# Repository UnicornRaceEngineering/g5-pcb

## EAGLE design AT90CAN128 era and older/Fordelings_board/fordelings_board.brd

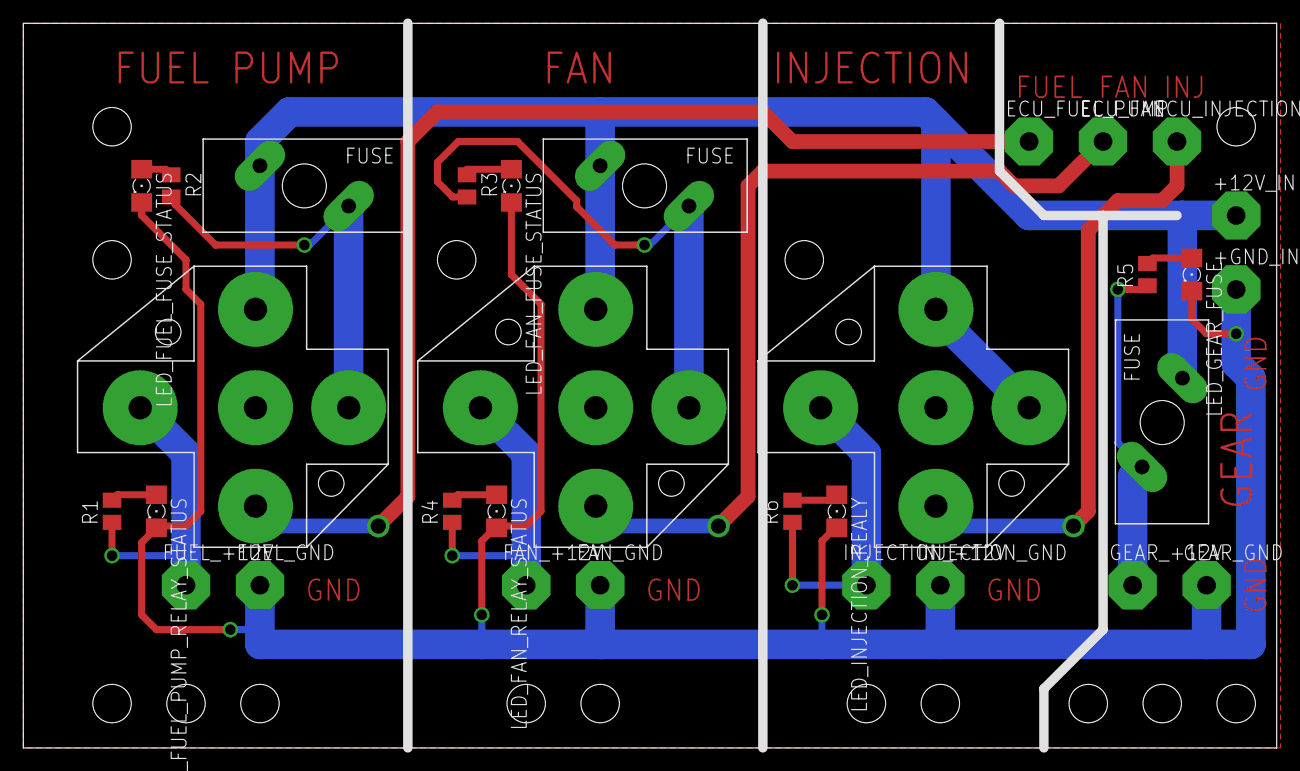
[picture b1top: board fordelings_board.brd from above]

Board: 2 copper layers, 107.6 x 62.2 mm, 46 parts (0 on the bottom side), 17 nets.

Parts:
+12V_IN: WIREPAD4,16O1,6; 4,16O1,6
+GND_IN: WIREPAD4,16O1,6; 4,16O1,6
ECU_FAN: WIREPAD4,16O1,6; 4,16O1,6
ECU_FUEL_PUMP: WIREPAD4,16O1,6; 4,16O1,6
ECU_INJECTION: WIREPAD4,16O1,6; 4,16O1,6
FAN_+12V: WIREPAD4,16O1,6; 4,16O1,6
FAN_GND: WIREPAD4,16O1,6; 4,16O1,6
FUEL_+12V: WIREPAD4,16O1,6; 4,16O1,6
FUEL_GND: WIREPAD4,16O1,6; 4,16O1,6
FUEL_PUMP_RELAY: FUSE_SOCKET; FUSE_SOCKET_12V_30A
GEAR_+12V: WIREPAD4,16O1,6; 4,16O1,6
GEAR_GND: WIREPAD4,16O1,6; 4,16O1,6
INJECTION_+12V: WIREPAD4,16O1,6; 4,16O1,6
INJECTION_GND: WIREPAD4,16O1,6; 4,16O1,6
JP1, JP2, JP3, JP4, JP5, JP6, JP7, JP8, JP9, JP10, JP11, JP12, JP13, JP14, JP15: STAND-OFF
LED_FAN_FUSE_STATUS: 1206
LED_FAN_RELAY_STATUS: 1206
LED_FUEL_FUSE_STATUS: 1206
LED_FUEL_PUMP_RELAY_STATUS: 1206
LED_GEAR_FUSE: 1206
LED_INJECTION_REALY: 1206
R1, R2, R3, R4, R5, R6: M0805
U$1, U$2: FUSE_SOCKET; FUSE_SOCKET_12V_30A
U$3, U$4, U$5: LITTE_FUSE; LITTE_FUSE_PAC

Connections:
+12V: +12V_IN.1, FUEL_PUMP_RELAY.P$4, U$1.P$1, U$1.P$4, U$2.P$4, U$3.P$1, U$4.P$2, U$5.P$2
ECU_FAN: ECU_FAN.1, U$2.P$2
ECU_FUEL_PUMP: ECU_FUEL_PUMP.1, FUEL_PUMP_RELAY.P$2
ECU_INJECTION: ECU_INJECTION.1, U$1.P$2
unnamed: FUEL_PUMP_RELAY.P$1, R2.2, U$4.P$1
unnamed: LED_FUEL_FUSE_STATUS.A, R2.1
unnamed: LED_FAN_RELAY_STATUS.A, R4.2
unnamed: R3.2, U$2.P$1, U$5.P$1
unnamed: INJECTION_+12V.1, R6.1, U$1.P$5
unnamed: GEAR_+12V.1, R5.1, U$3.P$2
unnamed: LED_GEAR_FUSE.A, R5.2
unnamed: LED_INJECTION_REALY.A, R6.2
unnamed: FAN_+12V.1, R4.1, U$2.P$5
unnamed: LED_FUEL_PUMP_RELAY_STATUS.A, R1.2
unnamed: FUEL_+12V.1, FUEL_PUMP_RELAY.P$5, R1.1
unnamed: LED_FAN_FUSE_STATUS.A, R3.1
PE: +GND_IN.1, FAN_GND.1, FUEL_GND.1, GEAR_GND.1, INJECTION_GND.1, LED_FAN_FUSE_STATUS.C, LED_FAN_RELAY_STATUS.C, LED_FUEL_FUSE_STATUS.C, LED_FUEL_PUMP_RELAY_STATUS.C, LED_GEAR_FUSE.C, LED_INJECTION_REALY.C

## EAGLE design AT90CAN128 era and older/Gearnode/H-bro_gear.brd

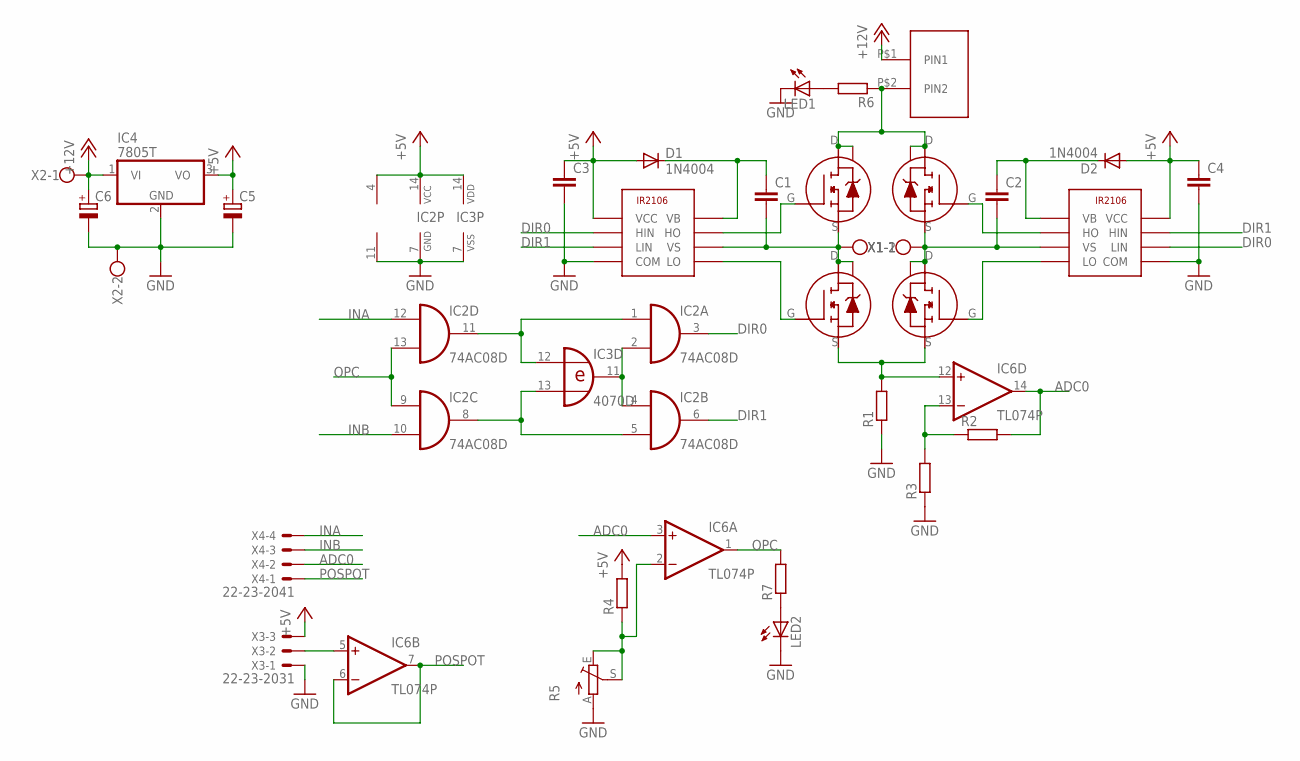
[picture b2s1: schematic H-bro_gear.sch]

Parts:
C1, C2, C3, C4: C-EU050-025X075; C050-025X075
C5, C6: CPOL-EUE15-5AXIAL; E15-5
D1, D2: 1N4004; DO41-10
IC2: 74AC08D; SO14
IC3: 4070D; SO14
IC4: 7805T; TO220H
IC6: TL074P; DIL14
LED1, LED2: LED5MM
R1: R-EU_0309/12; 0309/12
R2, R3, R4, R6, R7: R-EU_0204/7; 0204/7
R5: TRIM_EU-RJ9W; RJ9W
U$1, U$2: IR2106
U$3, U$4, U$5, U$6: STU95N5
U$7: LITTE_FUSE; LITTE_FUSE_PAC
X1, X2: W237-102
X3: 22-23-2031
X4: 22-23-2041

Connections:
+5V: C3.1, C4.1, C5.+, D1.A, D2.A, IC2.14 (VCC), IC3.14 (VDD), IC4.3 (VO), IC6.4 (V+), R4.2, U$1.VCC, U$2.VCC, X3.3
+12V: C6.+, IC4.1 (VI), U$7.P$1 (PIN1), X2.1
ADC0: IC6.3 (+IN), IC6.14 (OUT), R2.2, X4.2
DIR0: IC2.3 (O), U$1.HIN, U$2.LIN
DIR1: IC2.6 (O), U$1.LIN, U$2.HIN
GND: C3.2, C4.2, C5.-, C6.-, IC2.7 (GND), IC3.7 (VSS), IC4.2 (GND), IC6.11 (V-), LED1.K (C), LED2.K (C), R1.1, R3.1, R5.A, U$1.COM, U$2.COM, X2.2, X3.1
INA: IC2.12 (I0), X4.4
INB: IC2.10 (I1), X4.3
unnamed: U$1.HO, U$3.G
unnamed: U$1.LO, U$4.G
unnamed: U$2.HO, U$6.G
unnamed: U$2.LO, U$5.G
unnamed: C1.2, U$1.VS, U$3.S, U$4.D, U$4.TAB, X1.2
unnamed: C2.2, U$2.VS, U$5.D, U$5.TAB, U$6.S, X1.1
unnamed: R6.1, U$3.D, U$3.TAB, U$6.D, U$6.TAB, U$7.P$2 (PIN2)
unnamed: C1.1, D1.C, U$1.VB
unnamed: IC6.12 (+IN), R1.2, U$4.S, U$5.S
unnamed: C2.1, D2.C, U$2.VB
unnamed: IC2.2 (I1), IC2.4 (I0), IC3.11 (O)
unnamed: IC2.1 (I0), IC2.11 (O), IC3.12 (I0)
unnamed: IC2.5 (I1), IC2.8 (O), IC3.13 (I1)
unnamed: IC6.2 (-IN), R4.1, R5.E, R5.S
unnamed: LED1.A, R6.2
unnamed: IC6.5 (+IN), X3.2
unnamed: IC6.13 (-IN), R2.1, R3.2
unnamed: LED2.A, R7.1
OPC: IC2.9 (I0), IC2.13 (I1), IC6.1 (OUT), R7.2
POSPOT: IC6.6 (-IN), IC6.7 (OUT), X4.1

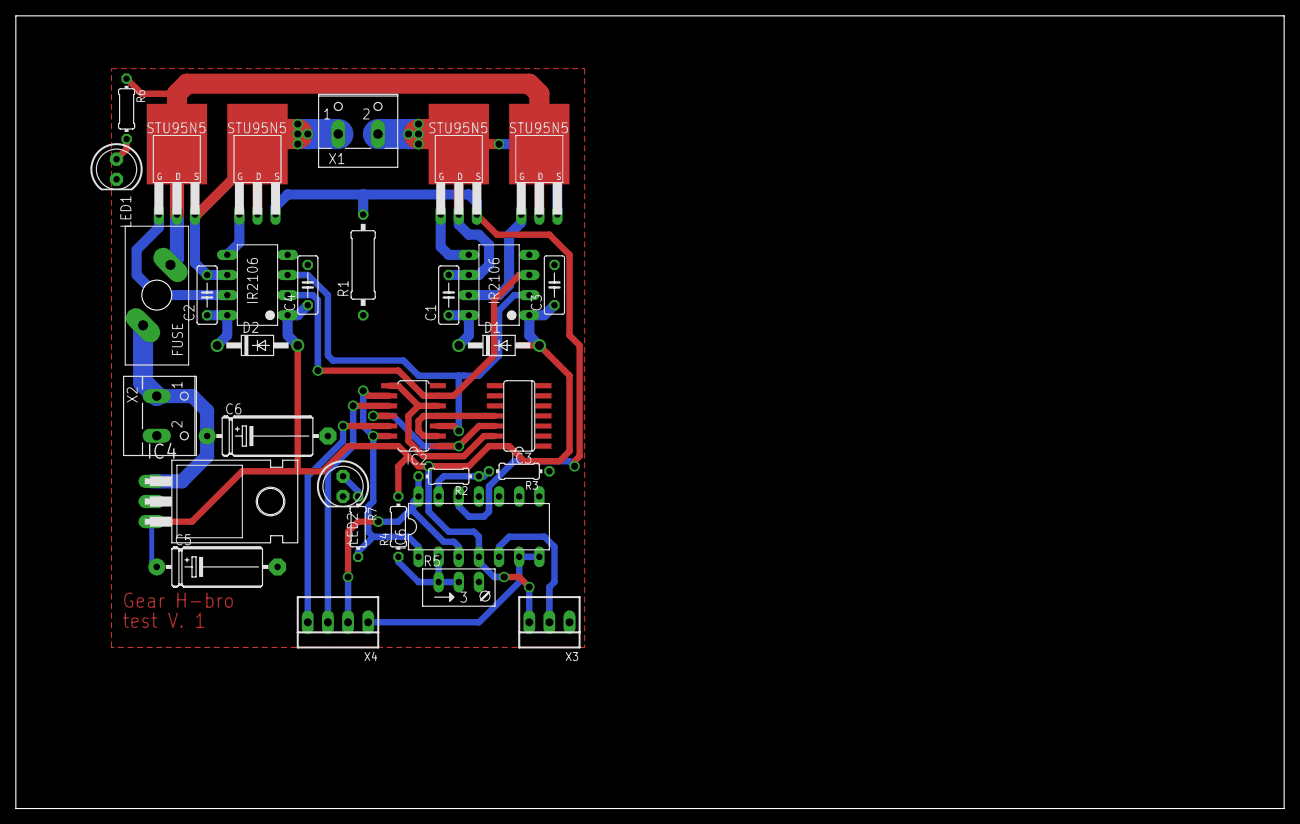
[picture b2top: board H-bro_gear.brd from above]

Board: 2 copper layers, 160.0 x 100.0 mm, 32 parts (0 on the bottom side), 28 nets.

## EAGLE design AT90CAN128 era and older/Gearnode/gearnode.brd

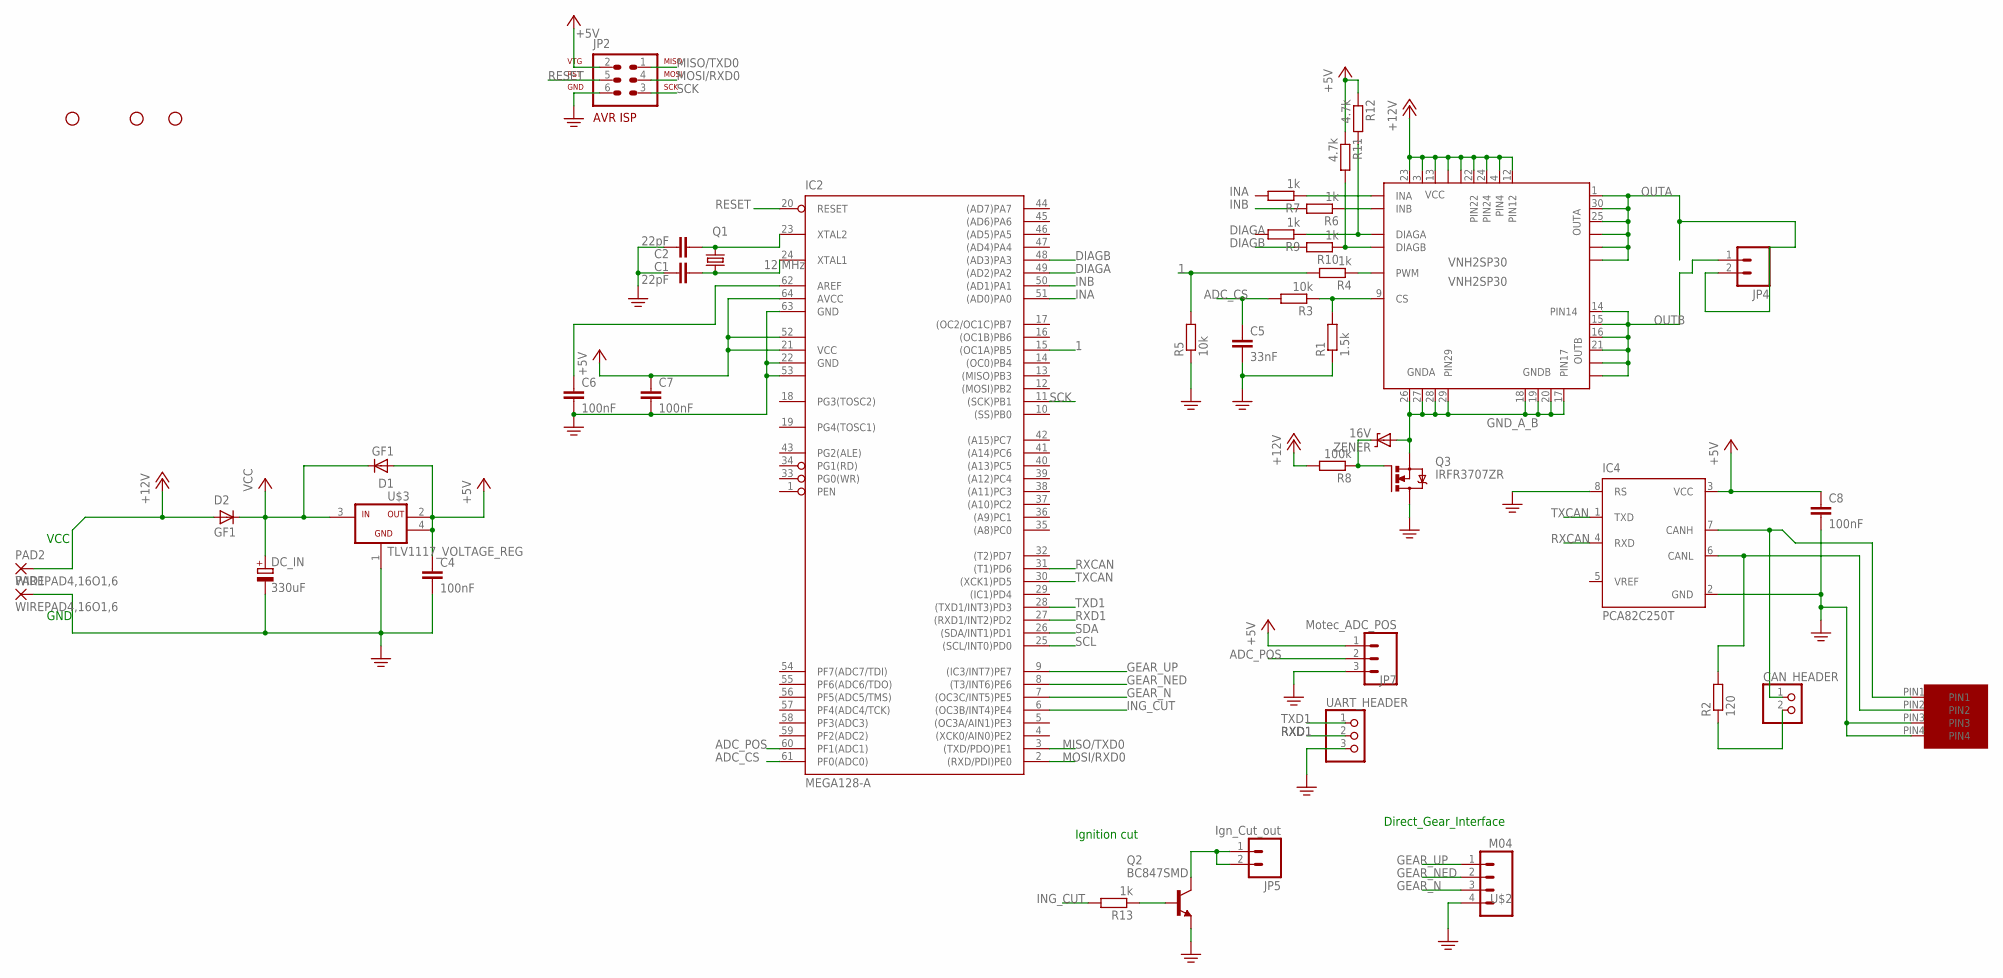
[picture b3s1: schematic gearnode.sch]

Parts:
C1, C2: 22pF; C5B2.5
C4, C6, C7, C8: 100nF; C0603K
C5: 33nF; C0603K
CAN_HEADER: PINHD-1X2; 1X02
D1, D2: GF1; SMA-DO214AC
DC_IN: 330uF; E15-5
IC2: MEGA128-A; TQFP64
IC4: PCA82C250T; SO8
JP1, JP3, JP6: STAND-OFF
JP2: AVR-ISP-6
JP4: M025MM; SCREWTERMINAL-5MM-2
JP5: Ign_Cut_out; S2B-PH
JP7: Motec_ADC_POS; S3B-PH
PAD1, PAD2: WIREPAD4,16O1,6; 4,16O1,6
Q1: 12 MHz; HC49U70
Q2: BC847SMD; SOT23
Q3: IRFR3707ZR; D-PAK_TO252AA
R1: 1.5k; R0603
R2: 120; R0603
R3, R5: 10k; R0603
R4, R6, R7, R9, R10, R13: 1k; R0603
R8: 100k; R0603
R11, R12: 4.7k; R0603
U$1: MICROFIT4; MICROFIT4SOCK
U$2: M04; S4B-PH
U$3: TLV1117_VOLTAGE_REG; SOT-232
UART_HEADER: PINHD-1X3; 1X03
VNH2SP30: VNH2SP30; MULTIPOWERSO-30
ZENER: 16V; SOD-323

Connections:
1: IC2.15 ((OC1A)PB5), R4.2, R5.2
+5V: C4.1, C7.1, C8.1, D1.A, IC2.21 (VCC), IC2.52 (VCC1), IC2.64 (AVCC), IC4.3 (VCC), JP2.2, JP7.1, R11.1, R12.1, U$3.2 (VOUT), U$3.4 (OUT2)
+12V: D2.A, PAD2.1, R8.2, VNH2SP30.3 (VCC), VNH2SP30.4 (PIN4), VNH2SP30.12 (PIN12), VNH2SP30.13 (VCC), VNH2SP30.22 (PIN22), VNH2SP30.23 (VCC), VNH2SP30.24 (PIN24), VNH2SP30.VCC, VNH2SP30.VCC@1 (VCC)
ADC_CS: C5.1, IC2.61 (PF0(ADC0)), R3.2
ADC_POS: IC2.60 (PF1(ADC1)), JP7.2
CANJUMP1: CAN_HEADER.1, IC4.7 (CANH), U$1.PIN1
CANJUMP2: CAN_HEADER.2, R2.1
DIAGA: IC2.49 ((AD2)PA2), R9.2
DIAGB: IC2.48 ((AD3)PA3), R10.2
GEAR_N: IC2.7 ((OC3C/INT5)PE5), U$2.3
GEAR_NED: IC2.8 ((T3/INT6)PE6), U$2.2
GEAR_UP: IC2.9 ((IC3/INT7)PE7), U$2.1
GND_A_B: Q3.3 (S), VNH2SP30.17 (PIN17), VNH2SP30.18 (GNDB), VNH2SP30.19 (GNDB), VNH2SP30.20 (GNDB), VNH2SP30.26 (GNDA), VNH2SP30.27 (GNDA), VNH2SP30.28 (GNDA), VNH2SP30.29 (PIN29), ZENER.2 (A)
INA: IC2.51 ((AD0)PA0), R7.2
INB: IC2.50 ((AD1)PA1), R6.2
ING_CUT: IC2.6 ((OC3B/INT4)PE4), R13.2
MISO/TXD0: IC2.3 ((TXD/PDO)PE1), JP2.1
MOSI/RXD0: IC2.2 ((RXD/PDI)PE0), JP2.4
unnamed: C1.2, IC2.24 (XTAL1), Q1.1
unnamed: C2.2, IC2.23 (XTAL2), Q1.2
unnamed: R4.1, VNH2SP30.8 (PWM)
unnamed: R1.2, R3.1, VNH2SP30.9 (CS)
unnamed: Q3.1 (G), R8.1, ZENER.1 (C)
unnamed: Q2.1 (B), R13.1
unnamed: C6.1, IC2.62 (AREF)
unnamed: JP5.1, JP5.2, Q2.3 (C)
unnamed: R9.1, R12.2, VNH2SP30.6 (DIAGA)
unnamed: R10.1, R11.2, VNH2SP30.10 (DIAGB)
unnamed: R7.1, VNH2SP30.5 (INA)
unnamed: R6.1, VNH2SP30.11 (INB)
unnamed: IC4.6 (CANL), R2.2, U$1.PIN2
OUTA: JP4.2, VNH2SP30.1 (OUTA), VNH2SP30.2 (PIN2), VNH2SP30.25 (OUTA), VNH2SP30.30 (OUTA), VNH2SP30.OUTA, VNH2SP30.OUTA@1 (OUTA)
OUTB: JP4.1, VNH2SP30.14 (PIN14), VNH2SP30.15 (OUTB), VNH2SP30.16 (OUTB), VNH2SP30.21 (OUTB), VNH2SP30.OUTB, VNH2SP30.OUTB@1 (OUTB)
PE: C1.1, C2.1, C4.2, C5.2, C6.2, C7.2, C8.2, DC_IN.-, IC2.22 (GND), IC2.53 (GND1), IC2.63 (GND), IC4.2 (GND), IC4.8 (RS), JP2.6, JP7.3, PAD1.1, Q2.2 (E), Q3.4 (D), R1.1, R5.1, U$1.PIN3, U$1.PIN4, U$2.4, U$3.1 (GND), UART_HEADER.3
RESET: IC2.20 (RESET), JP2.5
RXCAN: IC2.31 ((T1)PD6), IC4.4 (RXD)
RXD1: IC2.27 ((RXD1/INT2)PD2), UART_HEADER.2
SCK: IC2.11 ((SCK)PB1), JP2.3
SCL: IC2.25 ((SCL/INT0)PD0)
SDA: IC2.26 ((SDA/INT1)PD1)
TXCAN: IC2.30 ((XCK1)PD5), IC4.1 (TXD)
TXD1: IC2.28 ((TXD1/INT3)PD3), UART_HEADER.1
VCC: D1.K (C), D2.K (C), DC_IN.+, U$3.3 (VIN)

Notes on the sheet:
VCC
GND
Ignition cut
Direct_Gear_Interface

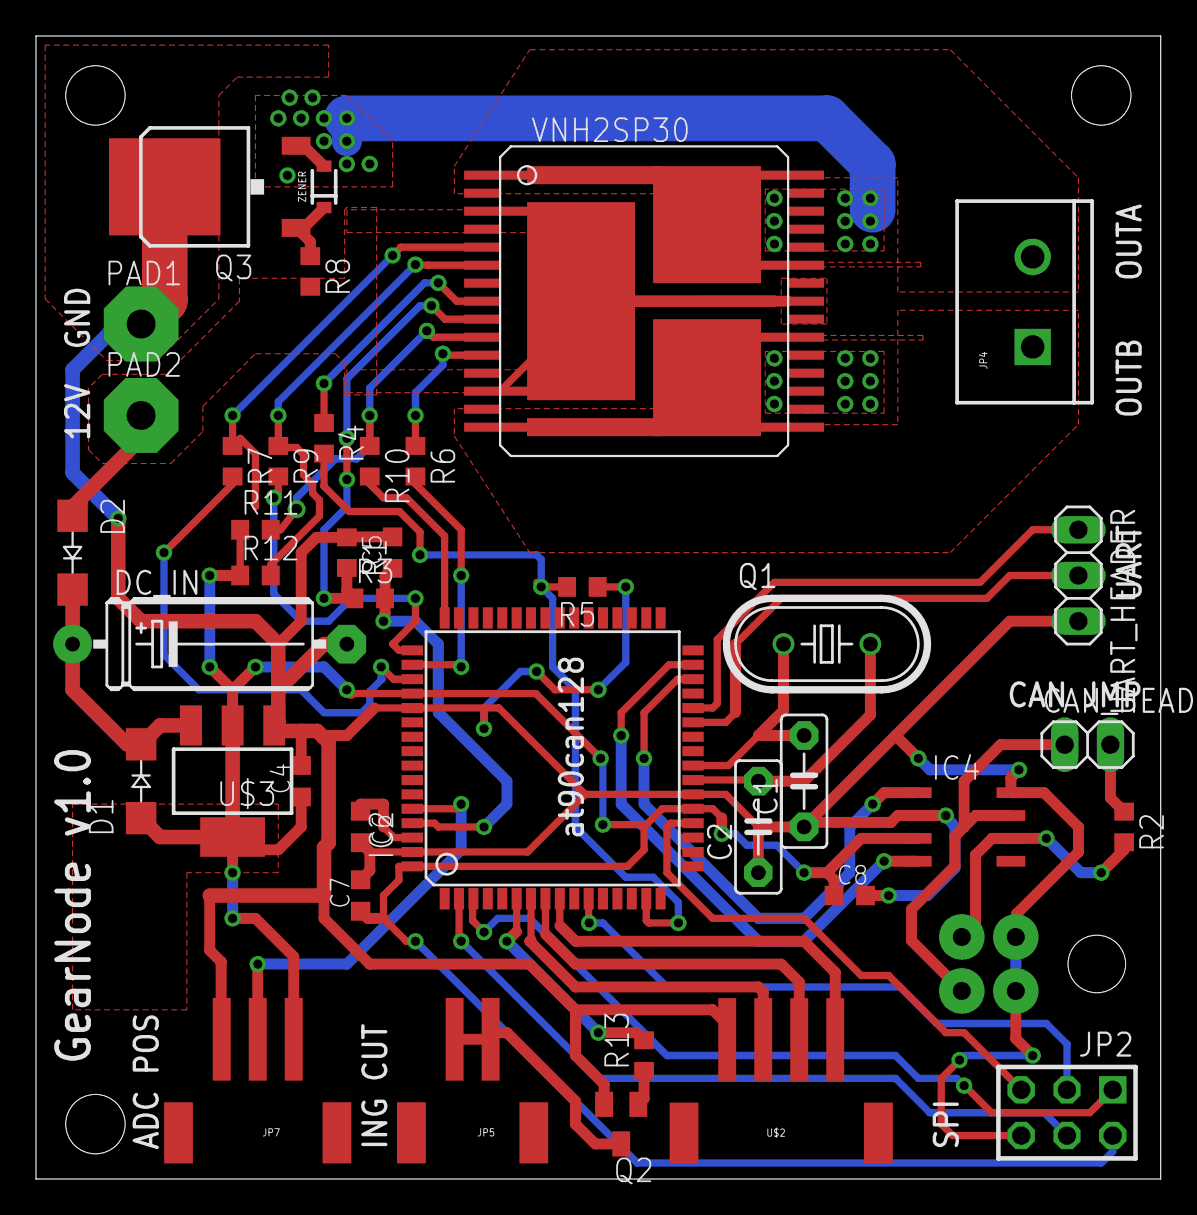
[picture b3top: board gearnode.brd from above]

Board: 2 copper layers, 62.5 x 63.5 mm, 44 parts (0 on the bottom side), 41 nets.

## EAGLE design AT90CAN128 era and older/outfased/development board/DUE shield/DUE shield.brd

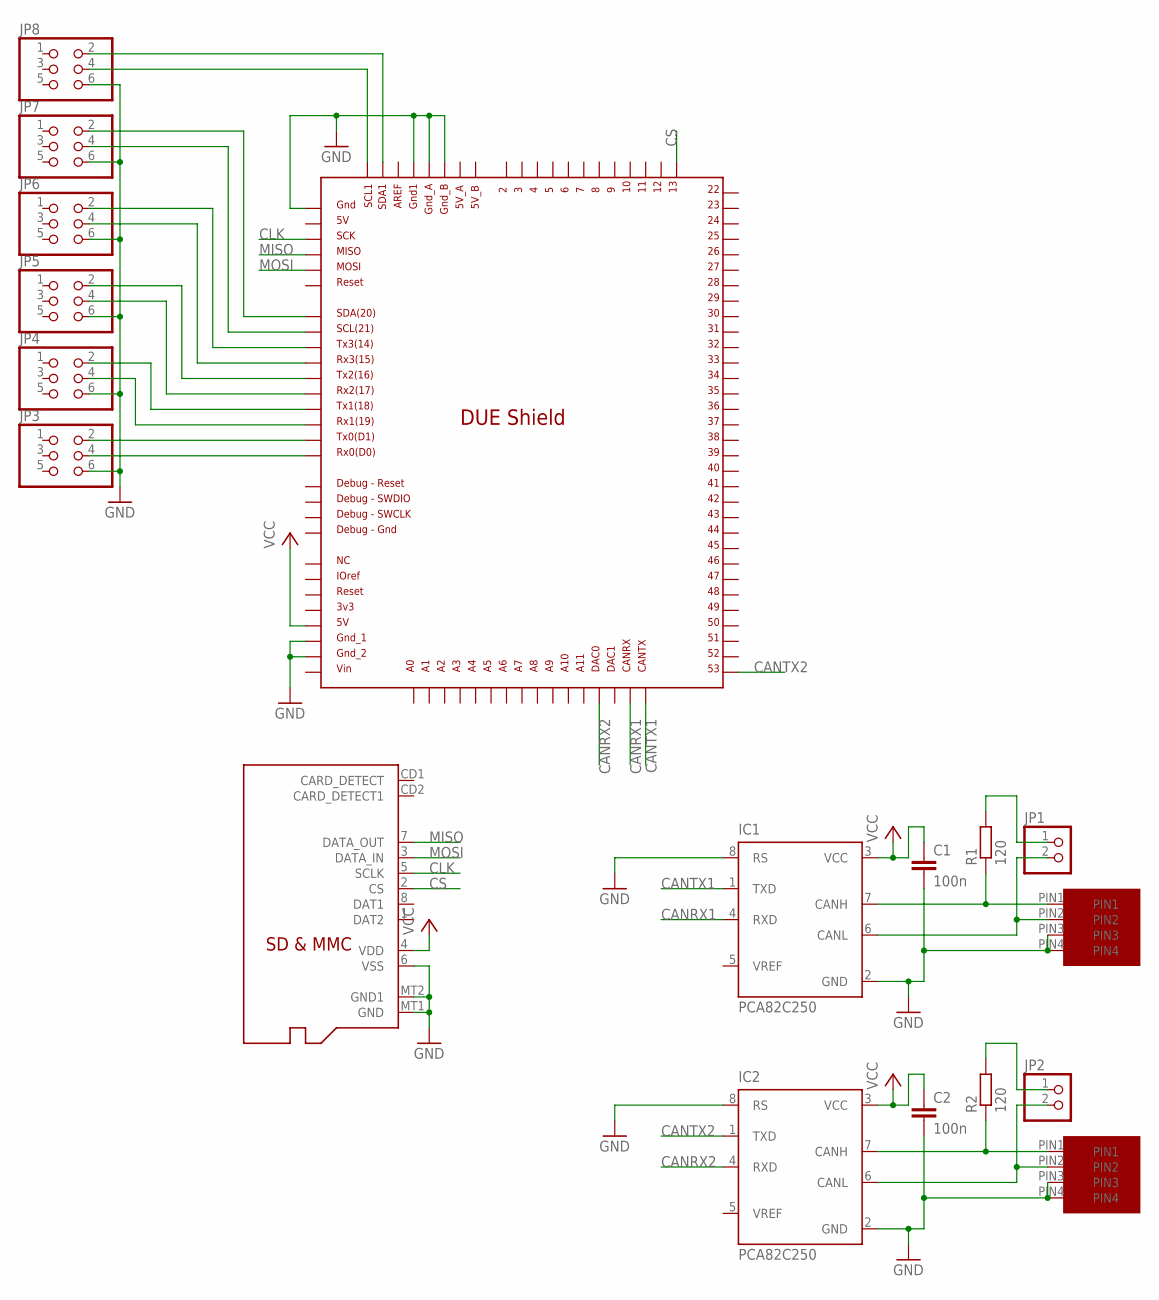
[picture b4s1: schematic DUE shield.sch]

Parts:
C1, C2: 100n; C050-024X044
IC1, IC2: PCA82C250; DIL08
JP1, JP2: PINHD-1X2; 1X02
JP3, JP4, JP5, JP6, JP7, JP8: PINHD-2X3; 2X03
R1, R2: 120; 0204/7
U$1: DUE(NORMAL)
U$2, U$3: MICROFIT4; MICROFIT4SOCK
U$4: MICROSD

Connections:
CANRX1: IC1.4 (RXD), U$1.CANRX
CANRX2: IC2.4 (RXD), U$1.DAC0
CANTX1: IC1.1 (TXD), U$1.CANTX
CANTX2: IC2.1 (TXD), U$1.53
CLK: U$1.SCK_ICSP, U$4.5 (SCLK)
CS: U$1.13, U$4.2 (CS)
GND: C1.2, C2.2, IC1.2 (GND), IC1.8 (RS), IC2.2 (GND), IC2.8 (RS), JP3.6, JP4.6, JP5.6, JP6.6, JP7.6, JP8.6, U$1.5V_ICSP, U$1.GND1, U$1.GND_1, U$1.GND_2, U$1.GND_A, U$1.GND_B, U$2.PIN3, U$2.PIN4, U$3.PIN3, U$3.PIN4, U$4.6 (VSS), U$4.MT1 (GND), U$4.MT2 (GND1)
MISO: U$1.MISO_ICSP, U$4.7 (DATA_OUT)
MOSI: U$1.MOSI_ICSP, U$4.3 (DATA_IN)
unnamed: IC1.7 (CANH), R1.1, U$2.PIN1
unnamed: IC1.6 (CANL), JP1.2, U$2.PIN2
unnamed: JP1.1, R1.2
unnamed: JP6.2, U$1.TX3
unnamed: IC2.7 (CANH), R2.1, U$3.PIN1
unnamed: IC2.6 (CANL), JP2.2, U$3.PIN2
unnamed: JP2.1, R2.2
unnamed: JP6.4, U$1.RX3
unnamed: JP5.2, U$1.TX2
unnamed: JP5.4, U$1.RX2
unnamed: JP4.2, U$1.TX1
unnamed: JP4.4, U$1.RX1
unnamed: JP3.2, U$1.TX0
unnamed: JP3.4, U$1.RX0
unnamed: JP7.4, U$1.SCL
unnamed: JP7.2, U$1.SDA
unnamed: JP8.4, U$1.SCL1
unnamed: JP8.2, U$1.SDA1
VCC: C1.1, C2.1, IC1.3 (VCC), IC2.3 (VCC), U$1.5V, U$4.4 (VDD)

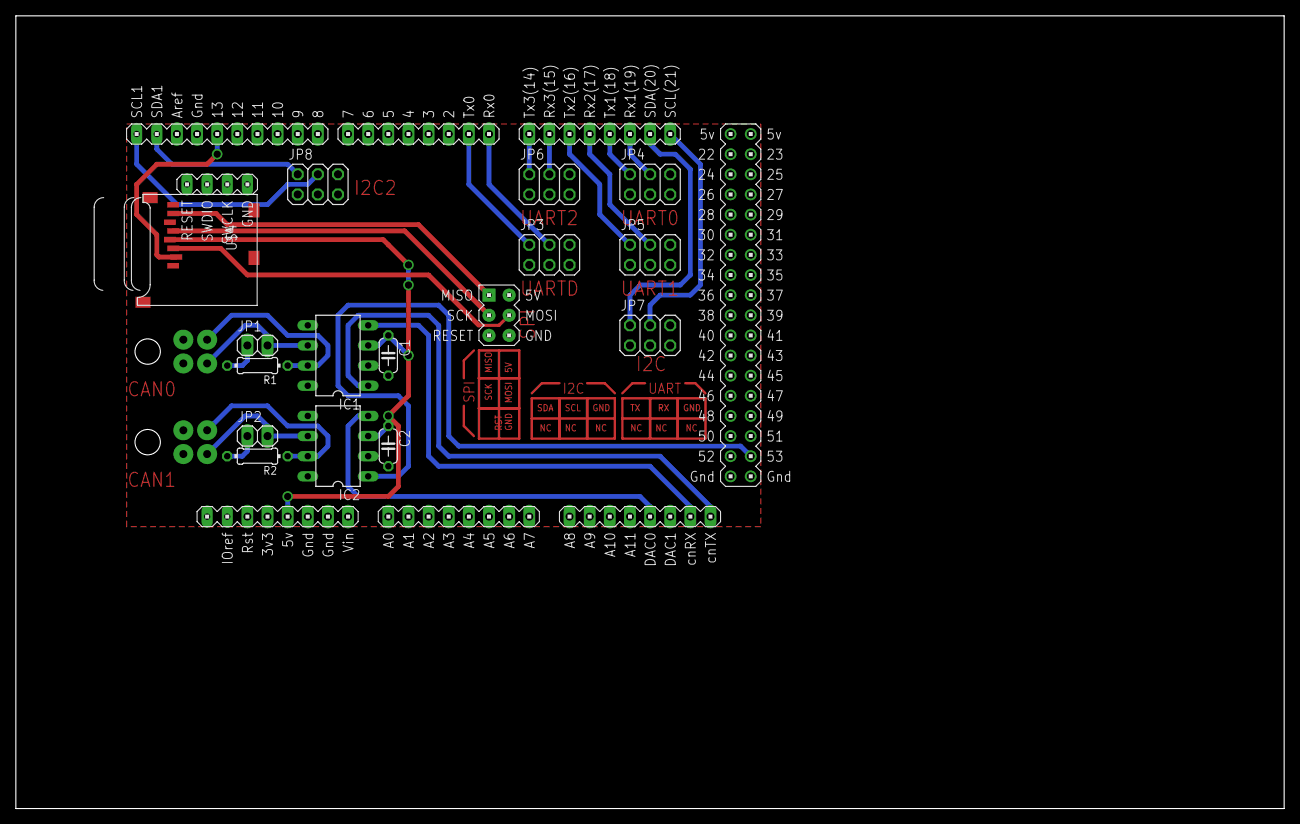
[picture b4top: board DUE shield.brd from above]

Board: 2 copper layers, 160.0 x 100.0 mm, 18 parts (0 on the bottom side), 28 nets.

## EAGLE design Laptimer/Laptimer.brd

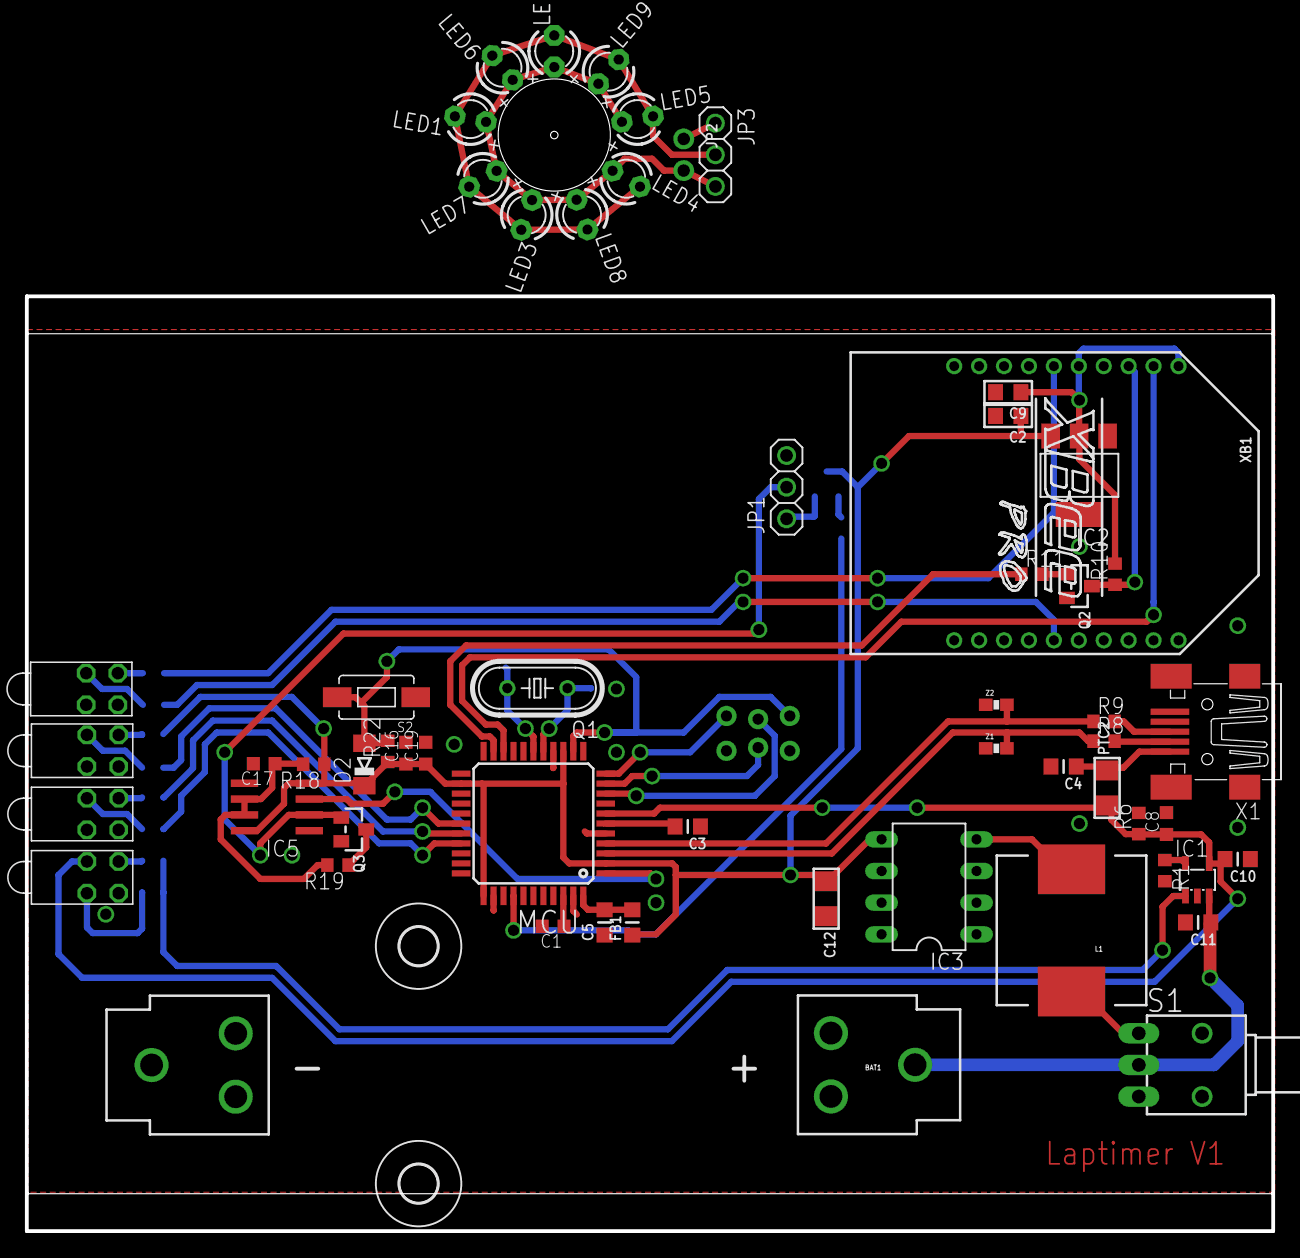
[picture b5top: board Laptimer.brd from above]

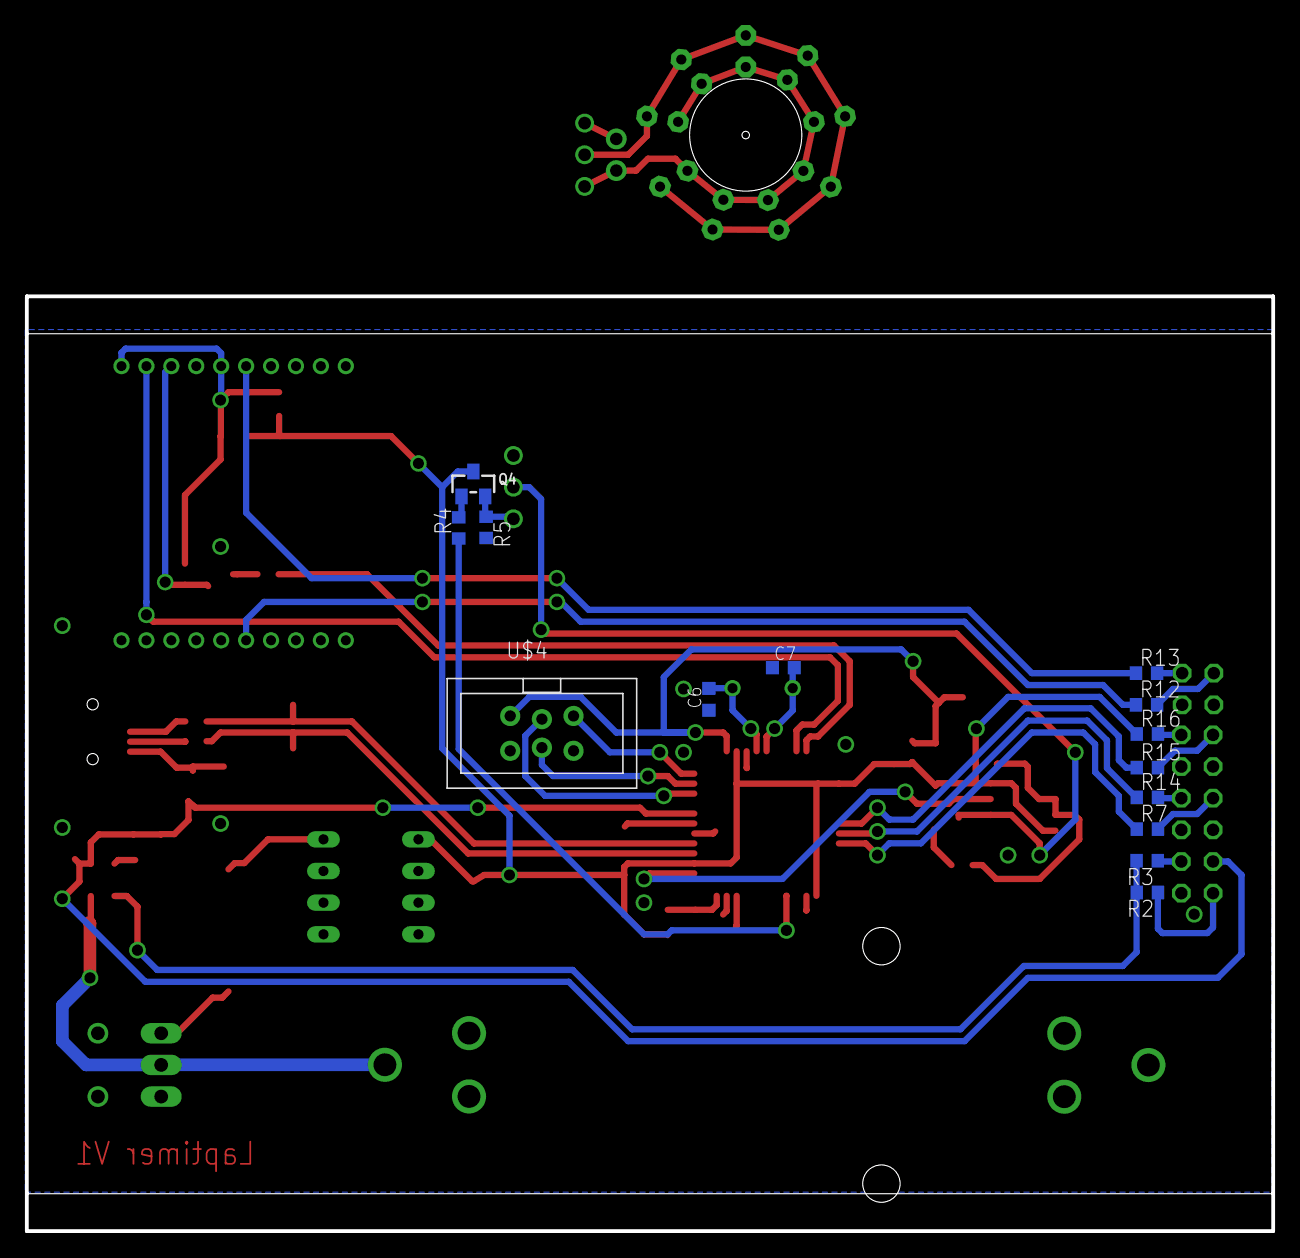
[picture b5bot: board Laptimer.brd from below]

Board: 2 copper layers, 100.0 x 75.0 mm, 73 parts (14 on the bottom side), 50 nets.

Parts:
BAT1: BATTERY_18650-HOLDER
C1, C8, C16, C17, C19: 100n; C0603K
C2: 10u; _0805
C3, C5: 1u; _0805MP
C4: 22u; _0805MP
C6, C7: 22pf; C0603K
C9: 22u; _0805
C10, C11: 10u; _0805MP
C12: 100u; 1206
D2: CD1206-S01575; MINIMELF
FB1: MH2029; _0805MP
H1, H2: MOUNT-HOLE3.0; 3,0
IC1: MCP73831/OT; SOT23-5L
IC2: REG1117; SOT223
IC3: MAX631CPA; DIL08
IC5: NE555D; SO08
JP1, JP3: 1X03
JP2: 1X02_ROUND
L1: DRA125-331-R; CDRH125
LED1, LED2, LED3, LED4, LED5, LED6, LED7, LED8, LED9: SFH 309; LED3MM
MCU: ATMEGA32U4-AU; TQFP44
PTC2: 1206
Q1: 8mhz; HC49/S
Q2, Q3: SOT23-WIDE
Q4: PBSS4120T; SOT23-WIDE
R1: 2k; R0603
R2: 470; R0603
R3, R4, R5, R10, R11, R18: 1k; R0603
R6, R22: 10k; R0603
R7, R12, R13, R14, R15, R16: 220; R0603
R8, R9: 22; R0603
R19: 100; R0603
S1: TL36WO; TL3XWO
S2: SWITCH-MOMENTARY-2-SMD-1101NE; TACTILE-SWITCH-1101NE
U$1, U$11, U$18, U$19: BI-LEVEL-LED-INDICATOR
U$4: AVRISP-BOX
X1: mini-usb; 32005-301
XB1: XBEE-PRO
Z1, Z2: CG0603MLC-05E; 0603-RES

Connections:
3.3V: C9.1, IC2.2, R10.2, XB1.1, XB1.5
5.0V: C2.1, C12.1, C16.1, C19.1, D2.C, FB1.1, IC2.3, IC3.5, IC5.4, IC5.8, MCU.2, MCU.14, MCU.24, MCU.34, Q4.3, R16.1, R18.1, R22.1
+UB: C8.1, C10.2, IC1.4, MCU.7, PTC2.1, R6.1, U$1.ANODE1
ASSOC: R12.1, XB1.15
CHRG-DONE-LED: R3.1, U$1.ANODE2
D+: MCU.4, R9.1, Z2.2
D-: MCU.3, R8.1, Z1.2
GND: BAT1.GND@1, C1.2, C2.2, C3.1, C4.2, C5.1, C6.1, C7.1, C8.2, C9.2, C10.1, C11.2, C12.2, C16.2, C17.2, C19.2, IC1.2, IC2.1, IC3.1, IC3.3, IC3.7, IC5.1, JP1.3, MCU.5, MCU.15, MCU.23, MCU.35, MCU.43, Q2.2, Q3.2, R1.2, R5.2, R6.2, S2.P$1, U$1.CATHODE2, U$4.6, U$11.CATHODE1, U$11.CATHODE2, U$18.CATHODE1, U$18.CATHODE2, U$19.CATHODE1, U$19.CATHODE2, X1.5, X1.M1, X1.M2, X1.M3, X1.M4, XB1.10, Z1.1, Z2.1
INT: JP3.2, LED1.K, LED2.K, LED3.K, LED4.K, LED5.K, LED6.K, LED7.K, LED8.K, LED9.K
LASER: MCU.37, R4.1
LED1: MCU.30, R7.1
LED2: MCU.29, R14.1
LED3: MCU.28, R15.1
MISO: MCU.11, U$4.1
MOSI: MCU.10, U$4.4
unnamed: R9.2, X1.3
unnamed: IC1.5, R1.1
unnamed: IC1.1, R2.2, R3.2
unnamed: JP1.1, Q4.2, R5.1
unnamed: Q4.1, R4.2
unnamed: C5.2, FB1.2, MCU.44
unnamed: C1.1, MCU.42
unnamed: JP2.1, JP3.1
unnamed: C3.2, MCU.6
unnamed: C4.1, PTC2.2, X1.1
unnamed: R2.1, U$1.CATHODE1
unnamed: R7.2, U$18.ANODE1
unnamed: R12.2, U$11.ANODE1
unnamed: Q2.1, R11.2
unnamed: R13.2, U$11.ANODE2
unnamed: R14.2, U$18.ANODE2
unnamed: IC3.4, L1.2
unnamed: R15.2, U$19.ANODE1
unnamed: L1.1, S1.1
unnamed: R8.2, X1.2
unnamed: BAT1.PWR@1, C11.1, IC1.3, S1.2
unnamed: R16.2, U$19.ANODE2
unnamed: C17.1, IC5.6, IC5.7, R18.2, R19.2
unnamed: JP2.2, JP3.3, LED1.A, LED2.A, LED3.A, LED4.A, LED5.A, LED6.A, LED7.A, LED8.A, LED9.A
unnamed: Q3.3, R19.1
PT-IN: IC5.2, JP1.2, Q3.1
PT-OUT: IC5.3, MCU.1
RSSI: R13.1, XB1.6
RST: D2.A, MCU.13, R22.2, S2.P$2, U$4.5
RX2: MCU.20, XB1.2
SCK: MCU.9, U$4.3
TX2: MCU.21, R11.1
TX2L: Q2.3, R10.1, XB1.3
XTAL1: C7.2, MCU.17, Q1.2
XTAL2: C6.2, MCU.16, Q1.1

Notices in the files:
parts and their libraries:
microbuilder: This work is placed in the public domain, and may be freely used for commercial and non-commercial work with the following conditions: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
SparkFun-Electromechanical: Licensing: Creative Commons ShareAlike 4.0 International - https://creativecommons.org/licenses/by-sa/4.0
